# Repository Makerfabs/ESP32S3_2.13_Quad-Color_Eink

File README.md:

# MaTouch ESP32-S3 2.13 Quad-Color Eink

## Introduction

Our MaTouch ESP32-S3 2.13 Quad-Color E-Ink display is equipped with the KEGM021317E08 model from Qingyue Optoelectronics, which adopts active matrix TFT microcapsule electrophoretic display technology to render images. This technology operates by applying an electric field to charged pigment particles suspended inside transparent microcapsules. Colored particles migrate to the microcapsule surfaces and reflect ambient light to form visible patterns, delivering a paper-like viewing experience identical to physical printed media. The EPD module features an active area resolution of 250(H) × 122(V) pixels, supporting 1-bit four-color display mode: black, white, red and yellow. Onboard peripheral expansion integrates the QMI8658A IMU sensor, which provides high-precision six-axis accelerometer and gyroscope data for motion detection, posture sensing and interactive control development.

Product Link: [MaTouch ESP32-S3 2.13 Quad-Color Eink](https://www.makerfabs.com/matouch-esp32-s3-2-13-quad-color-eink-epaper.html)

Wiki Link:  [MaTouch ESP32-S3 2.13 Quad-Color Eink](https://wiki.makerfabs.com/MaTouch%20ESP32_S3%202.13%20Quad_Color%20Eink.html)

Example：1.[SD_pic_display](https://github.com/Makerfabs/ESP32S3_2.13_Quad-Color_Eink#sd_pic_display)

2.[EPD_Pose_Display](https://github.com/Makerfabs/ESP32S3_2.13_Quad-Color_Eink#epd_pose_display)

## LCD Specs:

- PART NUMBER：KEGM021317E08
- SIZE：2.13 inch
- TYPE：Dot Matrix
- IC：JD79676
- RESOLUTION：250 × 122
- OUTLINE SIZE (mm)：75.2 × 29.2 × 0.911
- ACTIVE SIZE (mm)：48.55 × 23.7046
- PIXEL PITCH (mm)：0.1942 × 0.1943
- OPERATING TEMP.：0°C ~ 40°C
- STORAGE TEMP.：-25°C ~ 60°C
- CONNECTOR：24 Pin FPC
- COLOR：Black, White, Red, Yellow
- INTERFACE：SPI
- FULL REFRESH (S)：20

## Features

- Controller: ESP32-S3
- Wireless: WiFi& Bluetooth 5.0
- Flash:16MB Flash
- PSRAM:8MB
- MICRO SD: Yes
- IMU:QMI8658A
- USB:1 * USB_native
- Arduino support: Yes

## Example

### SD_pic_display

For details of this example, please refer to the [Wiki](https://wiki.makerfabs.com/MaTouch%20ESP32_S3%202.13%20Quad_Color%20Eink.html#41-sd_pic_display) document.

### EPD_Pose_Display

For details of this example, please refer to the [Wiki](https://wiki.makerfabs.com/MaTouch%20ESP32_S3%202.13%20Quad_Color%20Eink.html#42-epd_pose_display) document.

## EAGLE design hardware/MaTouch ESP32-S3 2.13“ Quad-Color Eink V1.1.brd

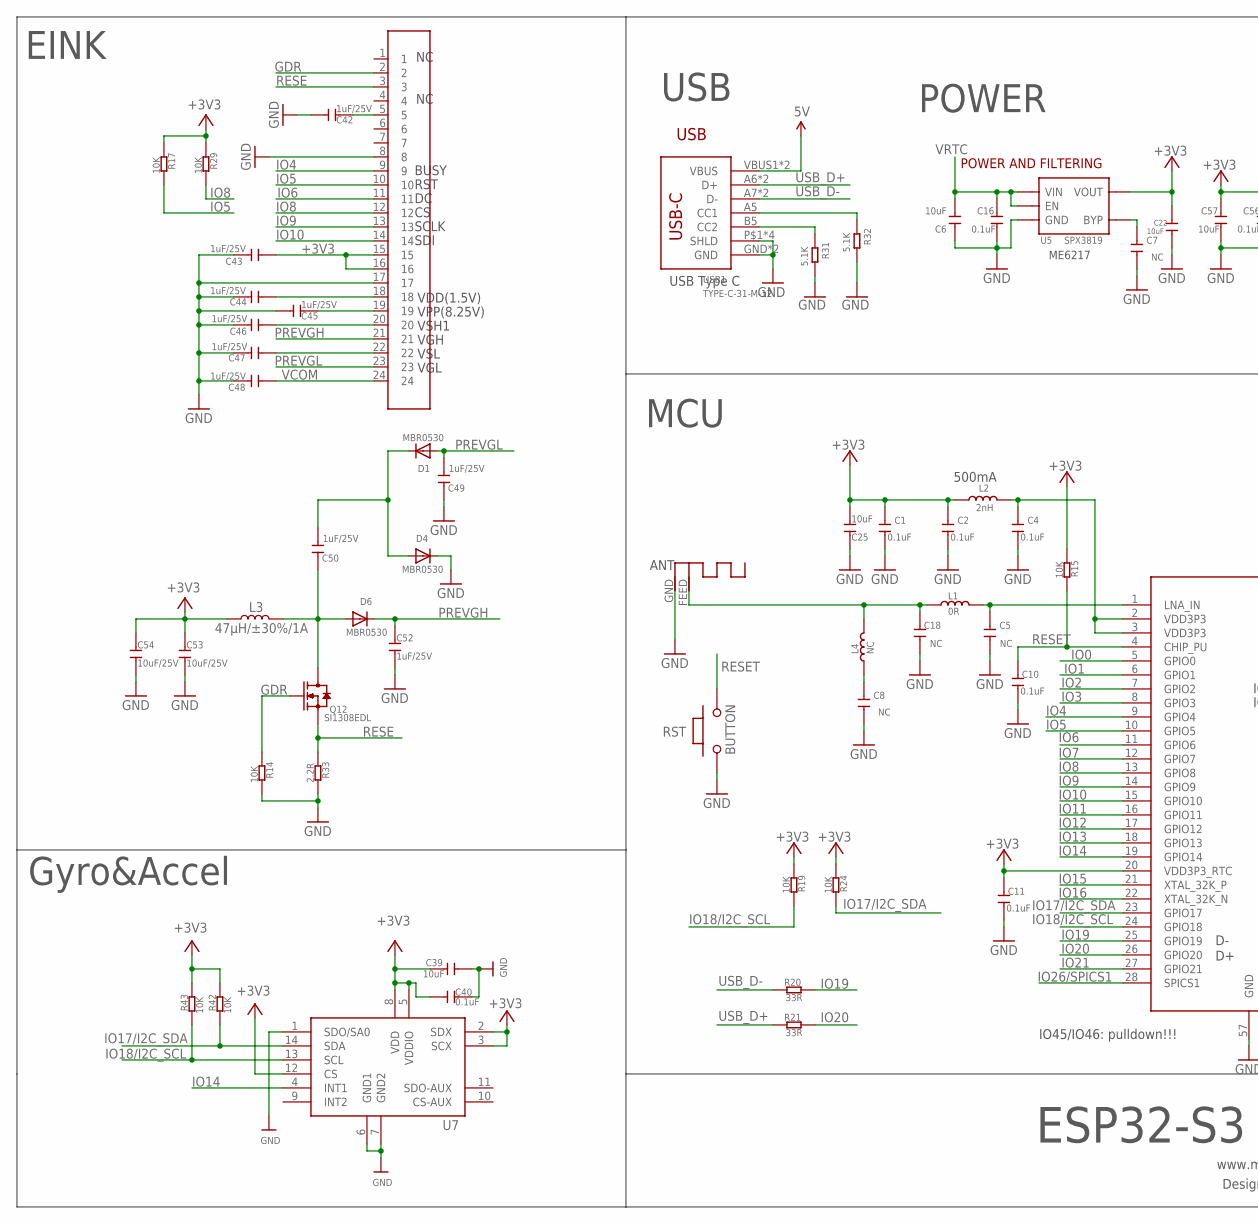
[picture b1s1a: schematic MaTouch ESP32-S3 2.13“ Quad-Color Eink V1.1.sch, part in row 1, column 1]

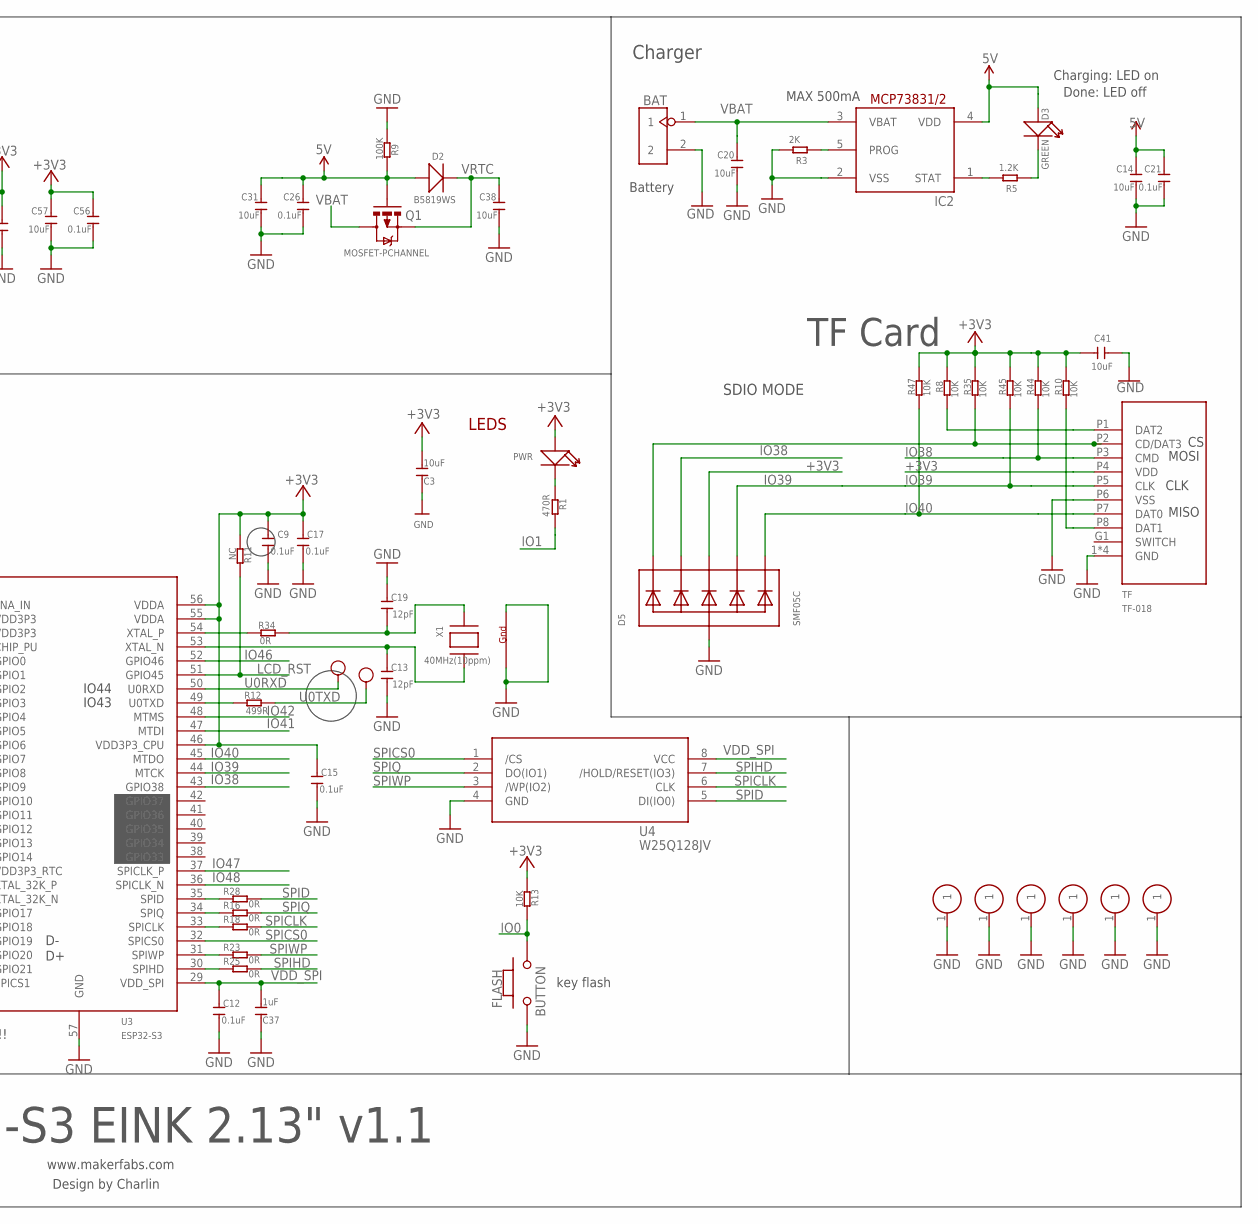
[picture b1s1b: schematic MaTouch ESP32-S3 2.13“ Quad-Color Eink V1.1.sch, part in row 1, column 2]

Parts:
ANT1: ANTENNA; RN-ANT
BAT: HEADER-2P-2.0; 2P-2.0
C1, C2, C4, C9, C10, C11, C12, C15, C16, C17, C21, C26, C40, C56: 0.1uF; DISCRETE_C0402
C3, C6, C25: 10uF; DISCRETE_C0603
C5, C7, C8, C18: NC; DISCRETE_C0402
C13, C19: 12pF; DISCRETE_C0402
C14, C20, C31, C38, C39, C41, C57: 10uF; DISCRETE_C0402
C22: 10uF; 0603
C37: 1uF; DISCRETE_C0603
C42, C43, C44, C45, C46, C47, C48, C49, C50: 1uF/25V; DISCRETE_C0402
C52: 1uF/25V; 0603
C53, C54: 10uF/25V; 0603
D1, D4, D6: MBR0530; SOD-323F
D2: B5819WS; SOD323
D3: GREEN; DISCRETE_LED-0603
D5: SMF05C; SOT363
FLASH: BUTTON; 157SW
IC2: TP4054; SOT23-5L
J1: FPC24-80P-A; SMD24-80P-1960L440W
L1: 0R; DISCRETE_L0402
L2: 2nH; DISCRETE_L0603
L3: 47µH/±30%/1A; CR54
L4: NC; DISCRETE_L0402
PWR: DISCRETE_LED0603; DISCRETE_LED-0603
Q1: MOSFET-PCHANNEL; SOT23-3
Q12: SI1308EDL; SOT23
R1: 470R; DISCRETE_R0402
R3: 2K; DISCRETE_R0402
R5: 1.2K; DISCRETE_R0402
R8, R10, R13, R14, R15, R17, R19, R24, R29, R35, R42, R43, R44, R45, R47: 10K; DISCRETE_R0402
R9: 100K; DISCRETE_R0402
R11: NC; DISCRETE_R0402
R12: 499R; DISCRETE_R0402
R16, R18, R23, R25, R28, R34: 0R; DISCRETE_R0402
R20, R21: 33R; DISCRETE_R0402
R31, R32: 5.1K; DISCRETE_R0402
R33: 2.2R; DISCRETE_R0402
RST: BUTTON; 157SW
RX: TEST-POINT'4545'; TP-D45MIL; PARTNO DNP
S1, S2, S3, S4, S5, S6: ONEPIN01
TF: TF-018
TX: TEST-POINT'4545'; TP-D45MIL; PARTNO DNP
U3: ESP32-S3; QFN56-7*7MM
U4: W25Q128JV; SOIC-8-208MIL
U5: SPX3819; SOT23-5
U7: QMI8658A; LGA14-50P-300L250W86H
USB1: TYPE-C-31-M-12
X1: 40MHz(10ppm); NX3225

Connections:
5V: C14.2, C21.2, C26.2, C31.2, D2.+, D3.+, IC2.4 (VDD), Q1.1 (G), R9.2, USB1.VBUS1 (VBUS), USB1.VBUS2 (VBUS)
+3V3: C1.2, C2.2, C3.2, C9.2, C11.2, C15.2, C17.2, C22.1, C25.2, C39.2, C40.2, C41.2, C43.1, C53.1, C54.1, C56.2, C57.2, D5.4 (C3), J1.15, J1.16, L2.1, L3.P$1 (1), PWR.+, R8.2, R10.2, R11.2, R13.2, R15.2, R17.1, R19.2, R24.2, R29.1, R35.2, R42.2, R43.2, R44.2, R45.2, R47.2, TF.P4 (VDD), U3.20 (VDD3P3_RTC), U3.46 (VDD3P3_CPU), U3.55 (VDDA), U3.56 (VDDA), U5.5 (VOUT), U7.2 (SDX), U7.3 (SCX), U7.5 (VDDIO), U7.8 (VDD), U7.12 (CS)
GDR: J1.2, Q12.1 (G), R14.1
GND: ANT1.GND, BAT.2, C1.1, C2.1, C3.1, C4.1, C5.1, C6.1, C7.1, C8.1, C9.1, C10.1, C11.1, C12.1, C13.1, C14.1, C15.1, C16.1, C17.1, C18.1, C19.2, C20.1, C21.1, C22.2, C25.1, C26.1, C31.1, C37.1, C38.1, C39.1, C40.1, C41.1, C42.2, C43.2, C44.2, C45.2, C46.2, C47.2, C48.2, C49.2, C52.2, C53.2, C54.2, C56.1, C57.1, D4.C, D5.2 (A), FLASH.1, IC2.2 (VSS), J1.8, J1.17, R3.2, R9.1, R14.2, R31.2, R32.2, R33.2, RST.1, S1.1, S2.1, S3.1, S4.1, S5.1, S6.1, TF.1 (GND), TF.2 (GND), TF.3 (GND), TF.4 (GND), TF.P6 (VSS), U3.57 (GND), U4.4 (GND), U5.2 (GND), U7.1 (SDO/SA0), U7.6 (GND1), U7.7 (GND2), USB1.GND, USB1.GND2 (GND), USB1.P$1 (SHLD), USB1.P$2 (SHLD), USB1.P$3 (SHLD), USB1.P$4 (SHLD), X1.2 (G2), X1.4 (G1)
IO0: FLASH.2, R13.1, U3.5 (GPIO0)
IO1: R1.1, U3.6 (GPIO1)
IO2: U3.7 (GPIO2)
IO3: U3.8 (GPIO3)
IO4: J1.9, U3.9 (GPIO4)
IO5: J1.10, R17.2, U3.10 (GPIO5)
IO6: J1.11, U3.11 (GPIO6)
IO7: U3.12 (GPIO7)
IO8: J1.12, R29.2, U3.13 (GPIO8)
IO9: J1.13, U3.14 (GPIO9)
IO10: J1.14, U3.15 (GPIO10)
IO11: U3.16 (GPIO11)
IO12: U3.17 (GPIO12)
IO13: U3.18 (GPIO13)
IO14: U3.19 (GPIO14), U7.4 (INT1)
IO15: U3.21 (XTAL_32K_P)
IO16: U3.22 (XTAL_32K_N)
IO17/I2C_SDA: R24.1, R42.1, U3.23 (GPIO17), U7.14 (SDA)
IO18/I2C_SCL: R19.1, R43.1, U3.24 (GPIO18), U7.13 (SCL)
IO19: R20.1, U3.25 (GPIO19)
IO20: R21.1, U3.26 (GPIO20)
IO21: U3.27 (GPIO21)
IO26/SPICS1: U3.28 (SPICS1)
IO38: D5.3 (C2), R44.1, TF.P3 (CMD), U3.43 (GPIO38)
IO39: D5.5 (C4), R45.1, TF.P5 (CLK), U3.44 (MTCK)
IO40: D5.6 (C5), R47.1, TF.P7 (DAT0), U3.45 (MTDO)
IO41: U3.47 (MTDI)
IO42: U3.48 (MTMS)
IO46: U3.52 (GPIO46)
IO47: U3.37 (SPICLK_P)
IO48: U3.36 (SPICLK_N)
LCD_RST: R11.1, U3.51 (GPIO45)
unnamed: ANT1.FEED, C18.2, L1.1, L4.2
unnamed: C5.2, L1.2, U3.1 (LNA_IN)
unnamed: R28.2, U3.35 (SPID)
unnamed: C8.2, L4.1
unnamed: R32.1, USB1.A5 (CC1)
unnamed: C42.1, J1.5
unnamed: PWR.-, R1.2
unnamed: C45.1, J1.19
unnamed: C46.1, J1.20
unnamed: C47.1, J1.22
unnamed: C50.1, D1.C, D4.A
unnamed: R8.1, TF.P1 (DAT2)
unnamed: C44.1, J1.18
unnamed: IC2.5 (PROG), R3.1
unnamed: R10.1, TF.P8 (DAT1)
unnamed: D5.1 (C1), R35.1, TF.P2 (CD/DAT3)
unnamed: IC2.1 (STAT), R5.2
unnamed: D3.-, R5.1
unnamed: C4.2, L2.2, U3.2 (VDD3P3), U3.3 (VDD3P3)
unnamed: R31.1, USB1.B5 (CC2)
unnamed: R16.2, U3.34 (SPIQ)
unnamed: R34.2, U3.54 (XTAL_P)
unnamed: R18.2, U3.33 (SPICLK)
unnamed: R23.2, U3.31 (SPIWP)
unnamed: R25.2, U3.30 (SPIHD)
unnamed: R12.2, U3.49 (U0TXD)
unnamed: C13.2, U3.53 (XTAL_N), X1.3 (X2)
unnamed: C19.1, R34.1, X1.1 (X1)
unnamed: C50.2, D6.A, L3.P$2 (2), Q12.3 (D)
unnamed: C7.2, U5.4 (BYP)
PREVGH: C52.1, D6.C, J1.21
PREVGL: C49.1, D1.A, J1.23
RESE: J1.3, Q12.2 (S), R33.1
RESET: C10.2, R15.1, RST.2, U3.4 (CHIP_PU)
SPICLK: R18.1, U4.6 (CLK)
SPICS0: U3.32 (SPICS0), U4.1 (/CS)
SPID: R28.1, U4.5 (DI(IO0))
SPIHD: R25.1, U4.7 (/HOLD/RESET(IO3))
SPIQ: R16.1, U4.2 (DO(IO1))
SPIWP: R23.1, U4.3 (/WP(IO2))
U0RXD: RX.T, U3.50 (U0RXD)
U0TXD: R12.1, TX.T
USB_D+: R21.2, USB1.A6 (D+), USB1.B6 (D+)
USB_D-: R20.2, USB1.A7 (D-), USB1.B7 (D-)
VBAT: BAT.1, C20.2, IC2.3 (VBAT), Q1.3 (D)
VCOM: C48.1, J1.24
VDD_SPI: C12.2, C37.2, U3.29 (VDD_SPI), U4.8 (VCC)
VRTC: C6.2, C16.2, C38.2, D2.-, Q1.2 (S), U5.1 (VIN), U5.3 (EN)

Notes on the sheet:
www.makerfabs.com
Design by Charlin
LEDS
POWER AND FILTERING
key flash
ESP32-S3 EINK 2.13" v1.1
POWER
MCU
ME6217
500mA
IO45/IO46: pulldown!!!
IO43
IO44
ANT
USB
USB Type C
Battery
Charging: LED on
Done: LED off
Charger
MAX 500mA
Gyro&Accel
SDIO MODE
TF Card
MOSI
CLK
MISO
EINK
VDD(1.5V)
VPP(8.25V)
VSH1
VGH
VSL
VGL
BUSY
RST
SCLK
SDI

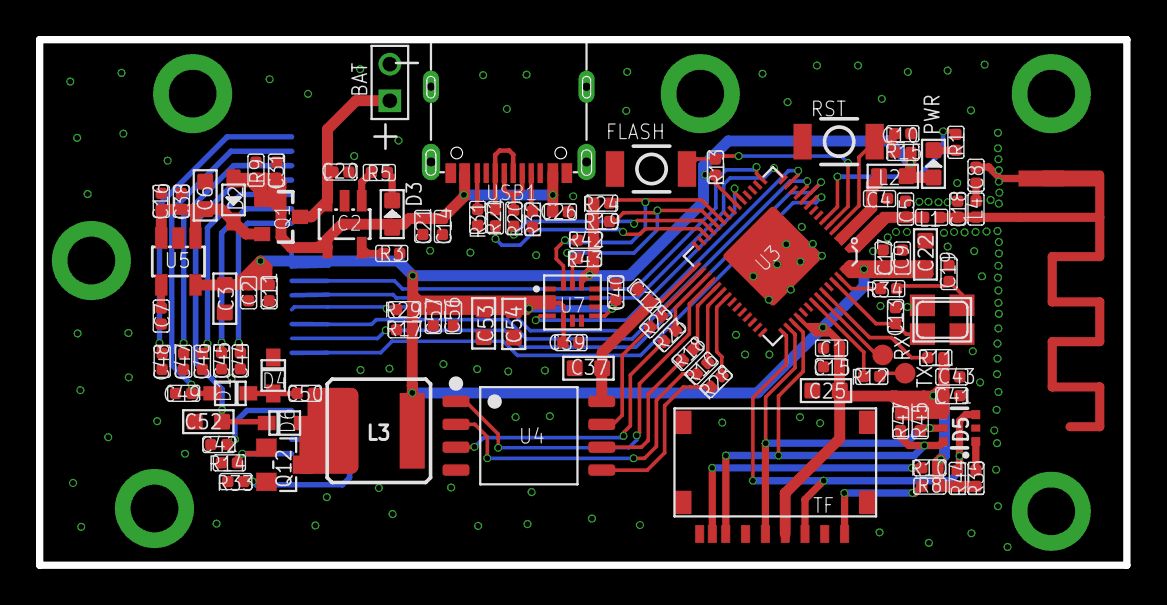
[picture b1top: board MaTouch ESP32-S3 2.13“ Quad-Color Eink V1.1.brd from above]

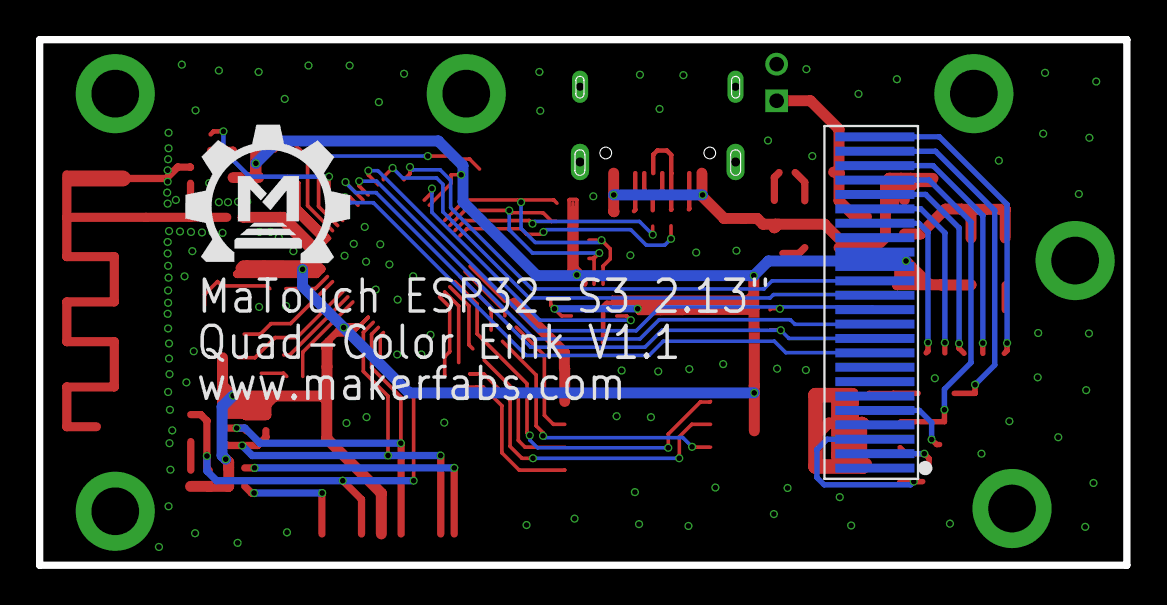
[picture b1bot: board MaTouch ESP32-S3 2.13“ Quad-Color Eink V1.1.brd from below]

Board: 2 copper layers, 60.4 x 29.2 mm, 111 parts (2 on the bottom side), 69 nets.

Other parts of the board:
U$1: MAKERFABS_0.3

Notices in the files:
parts and their libraries:
User-Submitted: Licensing: Creative Commons ShareAlike 4.0 International - https://creativecommons.org/licenses/by-sa/4.0
microbuilder: This work is placed in the public domain, and may be freely used for commercial and non-commercial work with the following conditions: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
